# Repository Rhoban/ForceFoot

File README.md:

# Force foot

**Note that this is the v2 version, you can have a look at the v1 branch for
the previous release**

Here is a design of a robot foot using strain gauges as force sensors.
It was used by the Rhoban Football Club (France) during the RoboCup 2016.

If you have any question feel free to contact team@rhoban.com to ask it,
or open an issue on this repository.

## Repository contents

Here are the repository contents, you can click on below links to get the documentation:

* A [**mechanical design**](3d) suitable for Rhoban robots, that can be a good base
  to be adapted to fit your needs;
* Schematics for an  [**electronics board**](electronics) containing all the components to get
  the values from the sensors and communicate them through dynamixel;
* A [**firmware**](firmware) for the controller that is on the electronics.

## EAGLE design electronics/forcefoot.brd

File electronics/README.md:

# Electronics

Here you'll find the schematics and (auto)routed board for sampling the gauge and communicate
through the dynamixel bus.

## Options

Some optional resistors on this board can be used to support dynamixel TTL/485 and 3/4 wire
gauges:

### Dynamixel RS485 or TTL

The two resistors (see yellow zones above) are only required if you want to use TTL Dynamixel.
In this case, you can solder a 3-pin connector on the dynamixel zone and it will do the job.

Actually, the A pin of the RS485 transciever is exactly the same as TTL when driving the line.
this change brings the B pin at VCC/2 (which should be 2.5V), so that when listening an high
A is 2.5V above B and a low A is 2.5V below B, which meets the RS485 requirements and makes
the MAX485 (or ST485) chip able to listen TTL, while perfectly respecting its specifications.

### 3-wire or 4-wire gauges

There is two main kind of mounting, half-bridges, which looks like that:

Here, there is three wire, so you'll have to compare the voltage value to 2.5V, this is why you
should solder the resistors (see cyan part of the above image) which will bring A- to V+/2 and
solder the third wire to A+.

The another option is a full-bridge:

We recommend this system since it is more accurate and robust. You'll have to solder the two
wires to A- and A+. The order of soldering doesn't really matter, since it will only affect the
sign of the measured value.

## Components

Here's a list of components you'll need to build the board with example links for buying them

### Controller

* ATmega328PB
* 16 Mhz HC49US quartz

### Resistors (all are 0805 package)

* 22 ohms
* 3 Kohms
* 8.2 Kohms
* 20 Kohms

### Capacitors (all are 0805 package)

* 1uF
* 0.2uF
* 22 pF

### Polar capacitor, for decoupling

* EEE1CA470SP: 47uF
* EEEFK1C221XP: 220uF

### Power 

You can buy a 7805, but we recommend using a switching instead, like the TRACO TSR 1-2450
to avoid intensive heating.

### ICs

The amps are HX711, a really widespread chip that is use in weight scales
This chips regulates the reference voltage for the amp, using an external
PNP transistor (SOT-23 package). S8550 or BC857B,215 can be used.

### Connectors for jauges

You can use any 1.5mm pitch connector you like. We recommend the
[JST-ZH 4P](https://fr.aliexpress.com/item/40-SETS-Mini-Micro-ZH-1-5-4-Pin-JST-Connector-with-Wires-Cables/32612842708.html?spm=2114.13010608.0.0.3bLgYh).

Note that the order of the pins, from left to right are:

    GND VCC A B

Which corresponds typically on cells to:

    BLACK RED WHITE GREEN

If you use only half bridge, do not connect the 3rd (white) pin, and solder the two
resistors that can apply VCC/2 on it.

[Continue through the docs with the firmware »](../firmware)

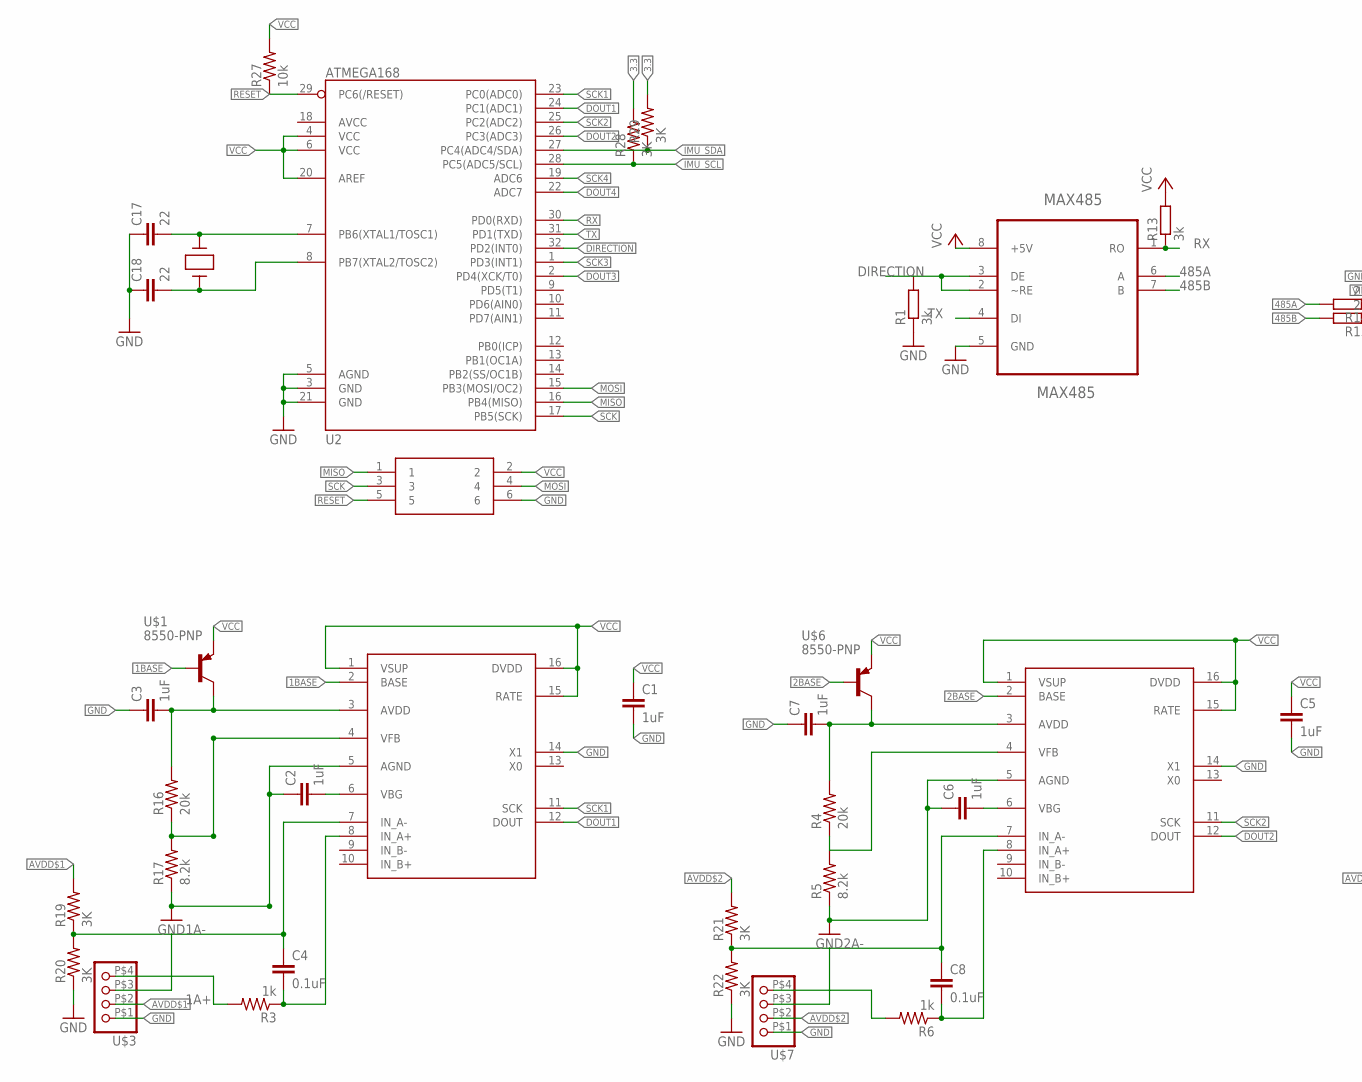
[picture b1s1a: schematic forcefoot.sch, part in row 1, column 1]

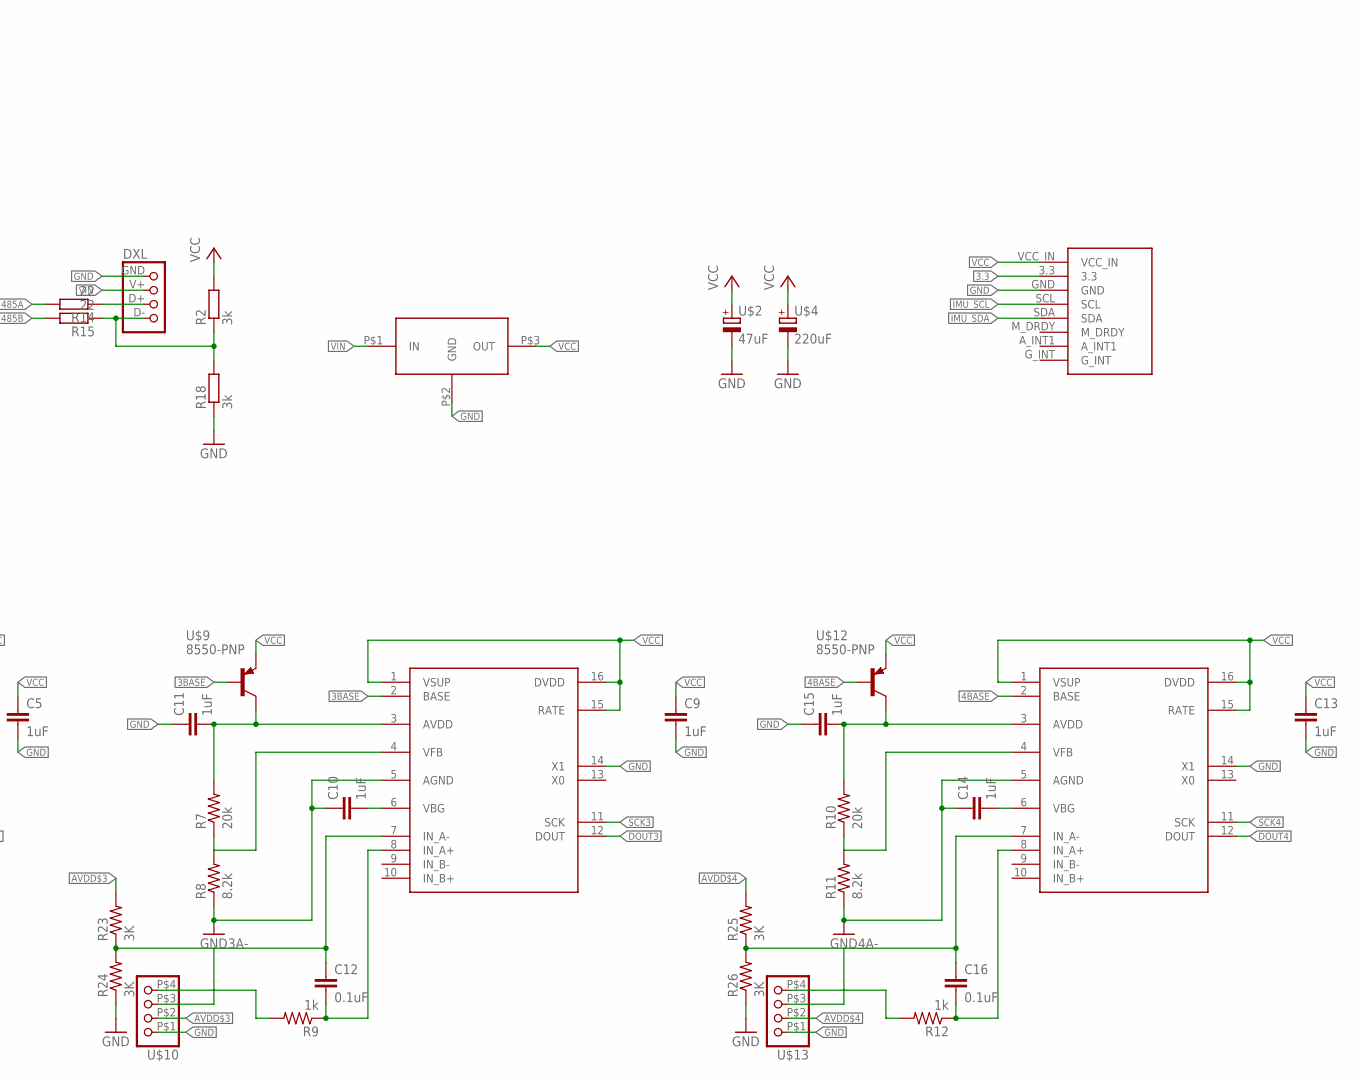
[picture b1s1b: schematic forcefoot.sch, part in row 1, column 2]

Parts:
C1, C2, C3, C5, C6, C7, C9, C10, C11, C13, C14, C15: 1uF; 0805; FARNELL 2525136RL
C4, C8, C12, C16: 0.1uF; 0805; FARNELL 2688486RL
C17, C18: 22; C0603; FARNELL 1759489RL
DXL: CONNEC_1X04_485; CONNEC_485; FARNELL 1104204 OR 9979620
HX1, HX2, HX3, HX4: HX711SO16; SO16; FARNELL HX711
IMU: GY-85
ISP: CONNEC_2X03; FARNELL 1593440
MAX485: MAX485; SO8; FARNELL 1564306
R1, R2, R13, R18: 3k; R0805; FARNELL 2074431
R3, R6, R9, R12: 1k; 0805; FARNELL 2074332RL
R4, R7, R10, R16: 20k; 0805; FARNELL 2074395
R5, R8, R11, R17: 8.2k; 0805; FARNELL 2074518
R14, R15: 22; R0805; FARNELL 2446926
R19, R20, R21, R22, R23, R24, R25, R26, R28, R29: 3K; 0805; FARNELL 2074431
R27: 10k; 0805; FARNELL 2074334RL
REG: REG_5V; TRACOPOWER; FARNELL 1696320
U2: ATMEGA168; TQFP32-08; FARNELL 2523203
U$1, U$6, U$9, U$12: 8550-PNP; SOT-23; FARNELL 1095136
U$2: 47uF; PANASONIC_D; FARNELL 9696946
U$3, U$7, U$10, U$13: CONNEC_1X041.5; 4P1.5; FARNELL 9491791
U$4: 220uF; PANASONIC_D8; FARNELL 1850103
XTAL1: QUARTZ; HC49US; FARNELL 7940506

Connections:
1A+: R3.2, U$3.P$4 (4)
1A-: C4.1, HX1.7 (IN_A-), R19.1, R20.2, U$3.P$3 (3)
1BASE: HX1.2 (BASE), U$1.1 (B)
2A-: C8.1, HX2.7 (IN_A-), R21.1, R22.2, U$7.P$3 (3)
2BASE: HX2.2 (BASE), U$6.1 (B)
3.3: IMU.3.3, R28.2, R29.2
3A-: C12.1, HX3.7 (IN_A-), R23.1, R24.2, U$10.P$3 (3)
3BASE: HX3.2 (BASE), U$9.1 (B)
4A-: C16.1, HX4.7 (IN_A-), R25.1, R26.2, U$13.P$3 (3)
4BASE: HX4.2 (BASE), U$12.1 (B)
485A: MAX485.6 (A), R14.2
485B: MAX485.7 (B), R15.2
AVDD$1: C3.2, HX1.3 (AVDD), R16.2, R19.2, U$1.3 (C), U$3.P$2 (2)
AVDD$2: C7.2, HX2.3 (AVDD), R4.2, R21.2, U$6.3 (C), U$7.P$2 (2)
AVDD$3: C11.2, HX3.3 (AVDD), R7.2, R23.2, U$9.3 (C), U$10.P$2 (2)
AVDD$4: C15.2, HX4.3 (AVDD), R10.2, R25.2, U$12.3 (C), U$13.P$2 (2)
DIRECTION: MAX485.2 (~RE), MAX485.3 (DE), R1.2, U2.32 (PD2(INT0))
DOUT1: HX1.12 (DOUT), U2.24 (PC1(ADC1))
DOUT2: HX2.12 (DOUT), U2.26 (PC3(ADC3))
DOUT3: HX3.12 (DOUT), U2.2 (PD4(XCK/T0))
DOUT4: HX4.12 (DOUT), U2.22 (ADC7)
GND: C1.2, C2.1, C3.1, C5.2, C6.1, C7.1, C9.2, C10.1, C11.1, C13.2, C14.1, C15.1, C17.1, C18.1, DXL.GND (1), HX1.5 (AGND), HX1.14 (X1), HX2.5 (AGND), HX2.14 (X1), HX3.5 (AGND), HX3.14 (X1), HX4.5 (AGND), HX4.14 (X1), IMU.GND, ISP.6, MAX485.5 (GND), R1.1, R5.1, R8.1, R11.1, R17.1, R18.1, R20.1, R22.1, R24.1, R26.1, REG.P$2 (GND), U2.3 (GND), U2.5 (AGND), U2.21 (GND), U$2.-, U$3.P$1 (1), U$4.-, U$7.P$1 (1), U$10.P$1 (1), U$13.P$1 (1)
IMU_SCL: IMU.SCL, R28.1, U2.28 (PC5(ADC5/SCL))
IMU_SDA: IMU.SDA, R29.1, U2.27 (PC4(ADC4/SDA))
INAP$1: C4.2, HX1.8 (IN_A+), R3.1
INAP$2: C8.2, HX2.8 (IN_A+), R6.1
INAP$3: C12.2, HX3.8 (IN_A+), R9.1
INAP$4: C16.2, HX4.8 (IN_A+), R12.1
MISO: ISP.1, U2.16 (PB4(MISO))
MOSI: ISP.4, U2.15 (PB3(MOSI/OC2))
unnamed: C2.2, HX1.6 (VBG)
unnamed: C6.2, HX2.6 (VBG)
unnamed: R6.2, U$7.P$4 (4)
unnamed: C10.2, HX3.6 (VBG)
unnamed: R9.2, U$10.P$4 (4)
unnamed: C14.2, HX4.6 (VBG)
unnamed: R12.2, U$13.P$4 (4)
unnamed: C17.2, U2.7 (PB6(XTAL1/TOSC1)), XTAL1.2
unnamed: C18.2, U2.8 (PB7(XTAL2/TOSC2)), XTAL1.1
RESET: ISP.5, R27.1, U2.29 (PC6(/RESET))
RS+: DXL.D+ (3), R14.1
RS-: DXL.D- (4), R2.1, R15.1, R18.2
RX: MAX485.1 (RO), R13.1, U2.30 (PD0(RXD))
SCK: ISP.3, U2.17 (PB5(SCK))
SCK1: HX1.11 (SCK), U2.23 (PC0(ADC0))
SCK2: HX2.11 (SCK), U2.25 (PC2(ADC2))
SCK3: HX3.11 (SCK), U2.1 (PD3(INT1))
SCK4: HX4.11 (SCK), U2.19 (ADC6)
TX: MAX485.4 (DI), U2.31 (PD1(TXD))
VCC: C1.1, C5.1, C9.1, C13.1, HX1.1 (VSUP), HX1.15 (RATE), HX1.16 (DVDD), HX2.1 (VSUP), HX2.15 (RATE), HX2.16 (DVDD), HX3.1 (VSUP), HX3.15 (RATE), HX3.16 (DVDD), HX4.1 (VSUP), HX4.15 (RATE), HX4.16 (DVDD), IMU.VCC_IN, ISP.2, MAX485.8 (+5V), R2.2, R13.2, R27.2, REG.P$3 (OUT), U2.4 (VCC), U2.6 (VCC), U2.20 (AREF), U$1.2 (E), U$2.+, U$4.+, U$6.2 (E), U$9.2 (E), U$12.2 (E)
VFB$1: HX1.4 (VFB), R16.1, R17.2
VFB$2: HX2.4 (VFB), R4.1, R5.2
VFB$3: HX3.4 (VFB), R7.1, R8.2
VFB$4: HX4.4 (VFB), R10.1, R11.2
VIN: DXL.V+ (2), REG.P$1 (IN)

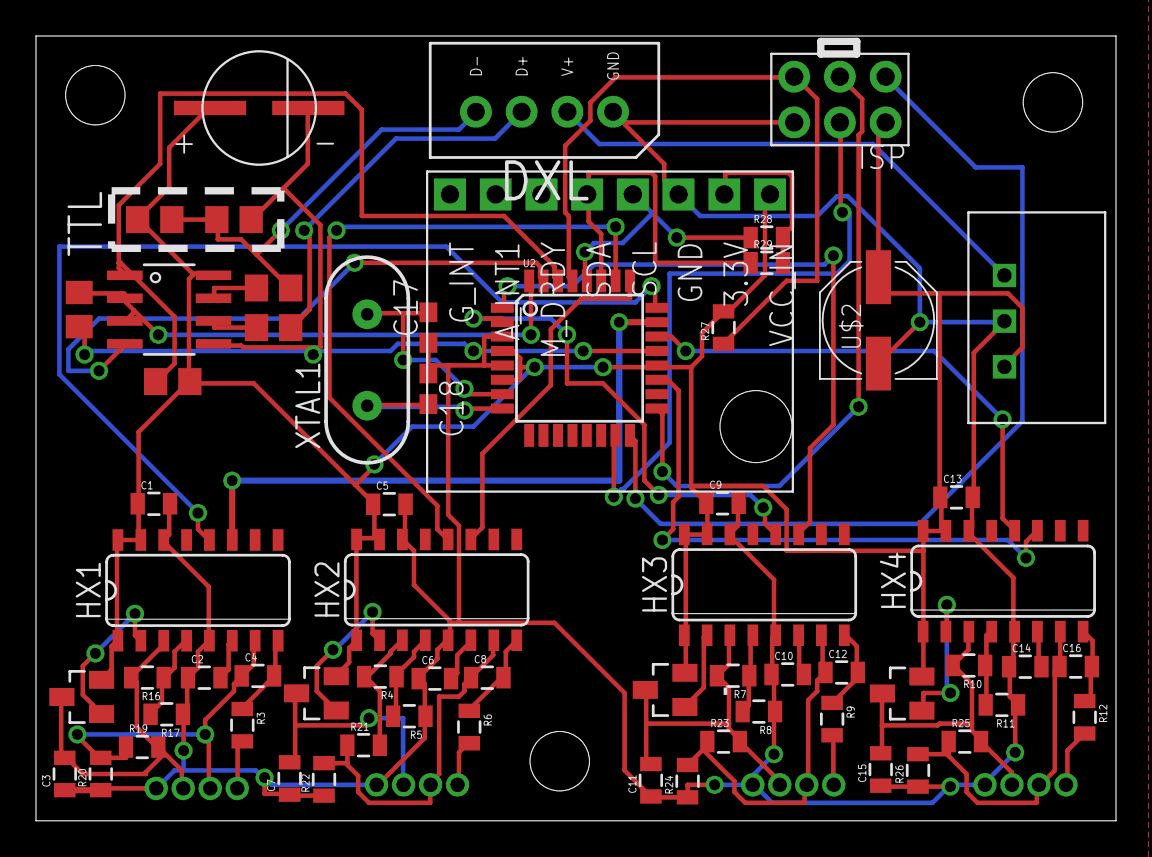
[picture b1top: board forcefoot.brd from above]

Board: 2 copper layers, 60.0 x 43.6 mm, 71 parts (0 on the bottom side), 55 nets.

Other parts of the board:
U$11, U$14, U$16: STAND-OFF

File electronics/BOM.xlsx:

|  |  | Rhoban HotSwap Board Bill of materials
 |  |  | For 3 pin dynamixel : solder R2 and R18, and user 3 pin connector For 4 pin dyn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
Item # | *Ref Des | *Qty | Manufacturer | *Mfg Part # | Description / Value | *Package | Type | Your Instructions / Notes
1 | R1, R13, R18, R19, R2, R20, R21, R22, R23, R24, R25, R26, R28, R29 | 14 | MULTICOMP | MCSR08X3001FTL | Resistor 3K | 0805 | SMD | Farnell : 2074431
2 | R10, R16, R4, R7 | 4 | MULTICOMP | MCSR08X2002FTL | Resistor 20k | 0805 | SMD | Farnell : 2074395
3 | R11, R17, R5, R8 | 4 | MULTICOMP | MCSR08X8201FTL | Resistor 8.2k | 0805 | SMD | Farnell : 2074518
4 | R14, R15 | 2 | MULTICOMP | MCWR08X22R0FTL | Resistor 22 Ohms | 0805 | SMD | Farnell : 2446926
5 | R12, R3, R6, R9 | 4 | MULTICOMP | MCSR08X1001FTL | Resistor 1K | 0805 | SMD | Farnell : 2074332RL
6 | R27 | 1 | MULTICOMP | MCSR08X1002FTL | Resistor 10k | 0805 | SMD | Farnell :2074334RL
7 | C1, C10, C11, C13, C14, C15, C2, C3, C5, C6, C7, C9 | 12 | TDK | C2012X5R1E105K125AA | Capacitor 1uF | 0805 | SMD | Farnell : 2525136RL
8 | C12, C16, C4, C8 | 4 | MURATA | GCM21BR72A104KA37K | Capacitor 0.1uF | 0805 | SMD | Farnell : 2688486RL
9 | C17, C18 | 2 | MULTICOMP | MC0805N220J201CT | Capacitor 22pF | 0805 | SMD | Farnell : 1759489RL
10 | U$4 | 1 | PANASONIC | EEEFK1C221XP | Capacitor 220uF | - | SMD | Farnell : 1850103
11 | U$2 | 1 | PANASONIC | EEE1CA470SP | Capacitor 47uF | - | SMD | Farnell : 9696946
12 | XTAL1 | 1 | ABRACON | ABLS-16.000MHZ-B2-T. | Crystal 16Mhz | HC-49US | Thru-Hole | Farnell : 7940506
13 | U$10, U$13, U$3, U$7 | 4 | JST | B4B-ZR(LF)(SN) | Connector 4 pins JST-ZH | - | Thru-Hole | Farnell : 9491791
14 | U2 | 1 | MICROCHIP | ATMEGA328PB-AU | ATmega328PB-AU microcontroller | TQFP-32 | SMD | Farnell : 2523203
15 | HX1, HX2, HX3, HX4 | 4 | AVIA SEMICONDUCTOR | HX711 | HX711 IC amp | SOIC16 | SMD | -
16 | DXL | 1 | MOLEX | 22-03-5035 (3 PIN) OR 22-03-5045 (4 PIN) | Dynamixel Connector (3 OR 4p) | - | Thru-Hole | Farnell : 1104204 OR 9979620
17 | U$1, U$12, U$6, U$9 | 4 | ON SEMICONDUCTOR | KST92MTF | PNP transistor | SOT-23 | SMD | Farnell : 1095136
18 | REG | 1 | TRACOPOWER | TSR 1-2450 | 5V 1A TRACOPOWER Regulator | - | Thru-Hole | Farnell : 1696320
19 | ISP | 1 | MULTICOMP | 2213S-06G | 2x6 0.1’’ male header | - | Thru-Hole | Farnell : 1593440
20 | MAX485 | 1 | STMICROELECTRONICS | ST485BDR | Transceiver RS422/RS485 | SOIC8 | SMD | Farnell : 1564306
Click for Instructions on How to Create a BOM

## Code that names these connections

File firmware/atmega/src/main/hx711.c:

#include <stdio.h>
#include <avr/io.h>
#include <util/delay.h>
#include <uart/dir.h>
#include "hx711.h"

int32_t hx711_values[4];

void hx711_clock_set(int index, int en)
{
    switch (index) {
        case 0:
            if (en) PORTC |= _BV(PC0);
            if (!en) PORTC &= ~_BV(PC0);
            break;
        case 1:
            if (en) PORTC |= _BV(PC2);
            if (!en) PORTC &= ~_BV(PC2);
            break;
        case 2:
            if (en) PORTD |= _BV(PD3);
            if (!en) PORTD &= ~_BV(PD3);
            break;
        case 3:
            if (en) PORTB |= _BV(PB0);
            if (!en) PORTB &= ~_BV(PB0);
            break;
    }
}

int hx711_read(int index)
{
    switch (index) {
        case 0:
            return ((PINC&_BV(PC1))!=0);
            break;
        case 1:
            return ((PINC&_BV(PC3))!=0);
            break;
        case 2:
            return ((PIND&_BV(PD4))!=0);
            break;
        case 3:
            return ((PINB&_BV(PB1))!=0);
            break;
    }
    return 0;
}

int hx711_available(int index)
{
    return !hx711_read(index);
}

#define VALUE_SIGN(value, length) \
        ((value < (1<<(length-1))) ? \
          (value) \
          : (value-(1<<length)))

int hx711_read_bit(int index)
{
    hx711_clock_set(index, 1);
    _delay_us(5);
    int result = hx711_read(index);
    hx711_clock_set(index, 0);
    _delay_us(5);
    return result;
}

int32_t hx711_sample(int index)
{
    uint32_t result = 0;
    int k;
    for (k=0; k<24; k++) {
        result <<= 1;
        result |= hx711_read_bit(index);
    }
    hx711_read_bit(index);

    uint32_t comp = 1;
    comp <<= 23;

    if (result < comp) {
        return result;
    } else {
        uint32_t shift = 1;
        shift <<= 24;
        return result - shift;
    }
}

static int current = 0;
void hx711_tick()
{
    if (hx711_available(current)) {
        hx711_values[current] = hx711_sample(current);
    }

    current++;
    if (current >= 4) current = 0;
}

void hx711_init()
{
    hx711_clock_set(0, 0);
    hx711_clock_set(1, 0);
    hx711_clock_set(2, 0);
    hx711_clock_set(3, 0);

    // Clocks as outputs
    DDRC |= _BV(PC0) | _BV(PC2);
    DDRD |= _BV(PD3);
    DDRB |= _BV(PB0);

    // Enabling pull up on inputs
    PORTC |= _BV(PC1) | _BV(PC3);
    PORTD |= _BV(PD4);
    PORTB |= _BV(PB1);
 
    /*
    // XXX: Debug: print all the values
    dir_set(1);
    _delay_ms(100);
    while (1) {
        int k;
        for (k=0; k<4; k++) {
            while (!hx711_available(k));
            printf("%ld\t", hx711_sample(k));
        }
        printf("\r\n");
    }
    */
}

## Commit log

2015-09-15 README
2015-09-15 Adding firmware
2015-09-15 Readme link
2015-09-16 Adding electronics
2015-09-16 electronics
2015-09-16 Board view
2015-09-16 3D design
2015-09-16 gitignore
2015-09-16 values
2015-09-18 Continue
2015-10-27 Tying AGND to GND
2015-10-27 Routable 8dof version
2015-10-27 Adding clock, tweaking placing
2015-10-27 Using 1.5mm 4p connectors
2015-10-27 Tying B-/B+ to ground
2015-11-17 Update schema
2015-11-19 Fixes
2016-03-29 Atmega+GY-85 version
2016-04-13 8dof firmware
2016-04-13 8dof
2016-04-13 Endianess
2016-04-18 Fixing pins...
2016-04-18 Firmware (wip)
2016-04-18 Board fixes
2016-04-19 dynamixel version
2016-04-24 pull ups
2016-06-19 Reducing delay
2016-06-19 sudo
2016-08-01 Moving connector
2017-03-20 board
2017-03-22 Tweaking for v2
2017-03-22 3d update
2017-03-22 V2 warning
2017-03-29 Detail
2017-05-19 Fixing r value
2017-05-22 Fixing vin -> vcc for mcu
2017-05-22 Fixing connections
2017-05-29 Update links
2017-05-30 Clarification on registers
2017-05-30 Clarifications
2017-05-30 rarr
2017-05-31 Added the possibility of return delay time define
2017-05-31 Improving names and silk
2018-02-14 mistake
2018-02-19 Gerber
2018-03-09 Adding support for ATmega328PB
2018-03-09 Adding support for m328pb fuses
2018-03-09 Readme note about 328pb
2018-03-16 TTL silk
2018-03-16 Using PORTE
2018-03-16 Atmega328PB
2018-08-30 Adding FARNELL attributes and writing BOM
2018-10-29 Centroids
2018-10-29 BOM for 3p
2018-10-29 SMT TH
2018-11-28 m328pb
2018-11-28 Binary firmware for 328PB (123 & 124)
2018-11-28 Flash script
2019-03-21 Updating atmega328pb for old ubuntus script
2019-03-21 Adding libc
2019-03-21 Headers
2019-12-16 Details about load cells and sigmaban public assembly
2022-04-15 There is no led
2022-04-15 Header re-alignment fix
2022-04-15 Supporting legacy pins

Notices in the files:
parts and their libraries:
SparkFun-Passives: Licensing: CC v3.0 Share-Alike You are welcome to use this library for commercial purposes.
SparkFun-DigitalIC: Licensing: Creative Commons ShareAlike 4.0 International - https://creativecommons.org/licenses/by-sa/4.0
